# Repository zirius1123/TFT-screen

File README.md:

# TFT Screen
I made a basic TFT screen for half life. It uses a basic 2.8" 240×320 SPI TFT with touch and a Rasberry Pi Pico. It also has 6 Cherry MX keys and one bourns slider pot.
## In depth description of components.
I am using kicad software and am using the 2.8" 240×320 SPI TFT with touch for the screen, which consists of the
* ILI9341 screen chip
* XPT2046 touch chip
I am also using
* A rasberry pi pico 2
* 6 Cherry MX
* 1 Bourns Slider pot
I also used 2 capacitors and 2 transistors
## Project showcase

These are the images of the projects pcb  and  schematic respectively.

Using JLCPCB for the PCB and aliexpress for the other components.

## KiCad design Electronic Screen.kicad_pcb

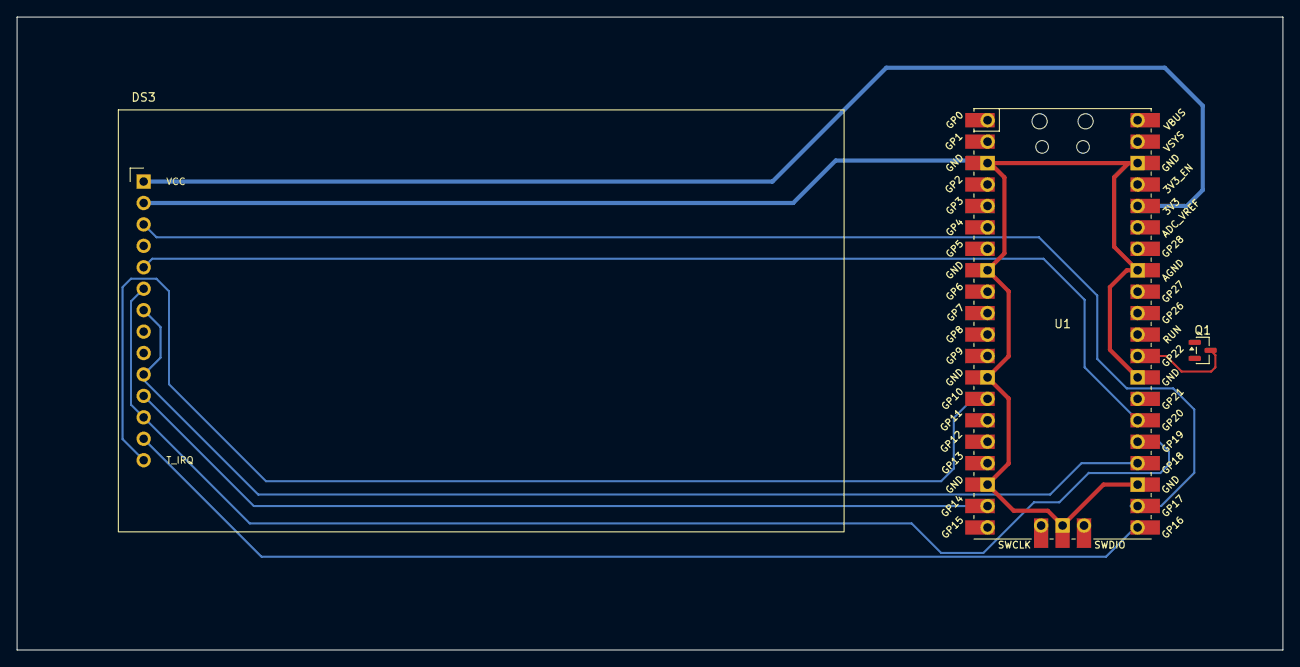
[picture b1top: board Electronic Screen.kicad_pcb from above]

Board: 2 copper layers, 150.0 x 75.0 mm, 3 parts (0 on the bottom side), 10 nets.

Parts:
DS3: ILI9341_2.8in_240x320_Touch; ILI9341_2.8in_240x320_Touch_Module
Q1: AO3401A; SOT-23
U1: Pico; RPi_Pico_SMD_TH

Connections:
+3V3: DS3.1 (VCC), U1.36 (3V3)
/CS: DS3.3 (CS), U1.22 (GPIO17)
/DC: DS3.5 (DC), U1.26 (GPIO20)
/MISO: DS3.13 (T_DO), U1.21 (GPIO16)
/MOSI: DS3.6 (SDI), DS3.12 (T_DIN), U1.25 (GPIO19)
/SCK: DS3.7 (SCK), DS3.10 (T_CLK), U1.24 (GPIO18)
/T_CS: DS3.11 (T_CS), U1.19 (GPIO14)
/T_IRQ: DS3.14 (T_IRQ), U1.14 (GPIO10)
GND: DS3.2 (GND), U1.3 (GND), U1.8 (GND), U1.13 (GND), U1.18 (GND), U1.23 (GND), U1.28 (GND), U1.33 (AGND), U1.38 (GND), U1.42 (GND)
unnamed: Q1.3 (D), U1.29 (GPIO22)
